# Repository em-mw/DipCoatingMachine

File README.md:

# DippingMachine

This is a instrument that is designed to dip an object into a solution

This instrument developed for TCH

-- em-mw

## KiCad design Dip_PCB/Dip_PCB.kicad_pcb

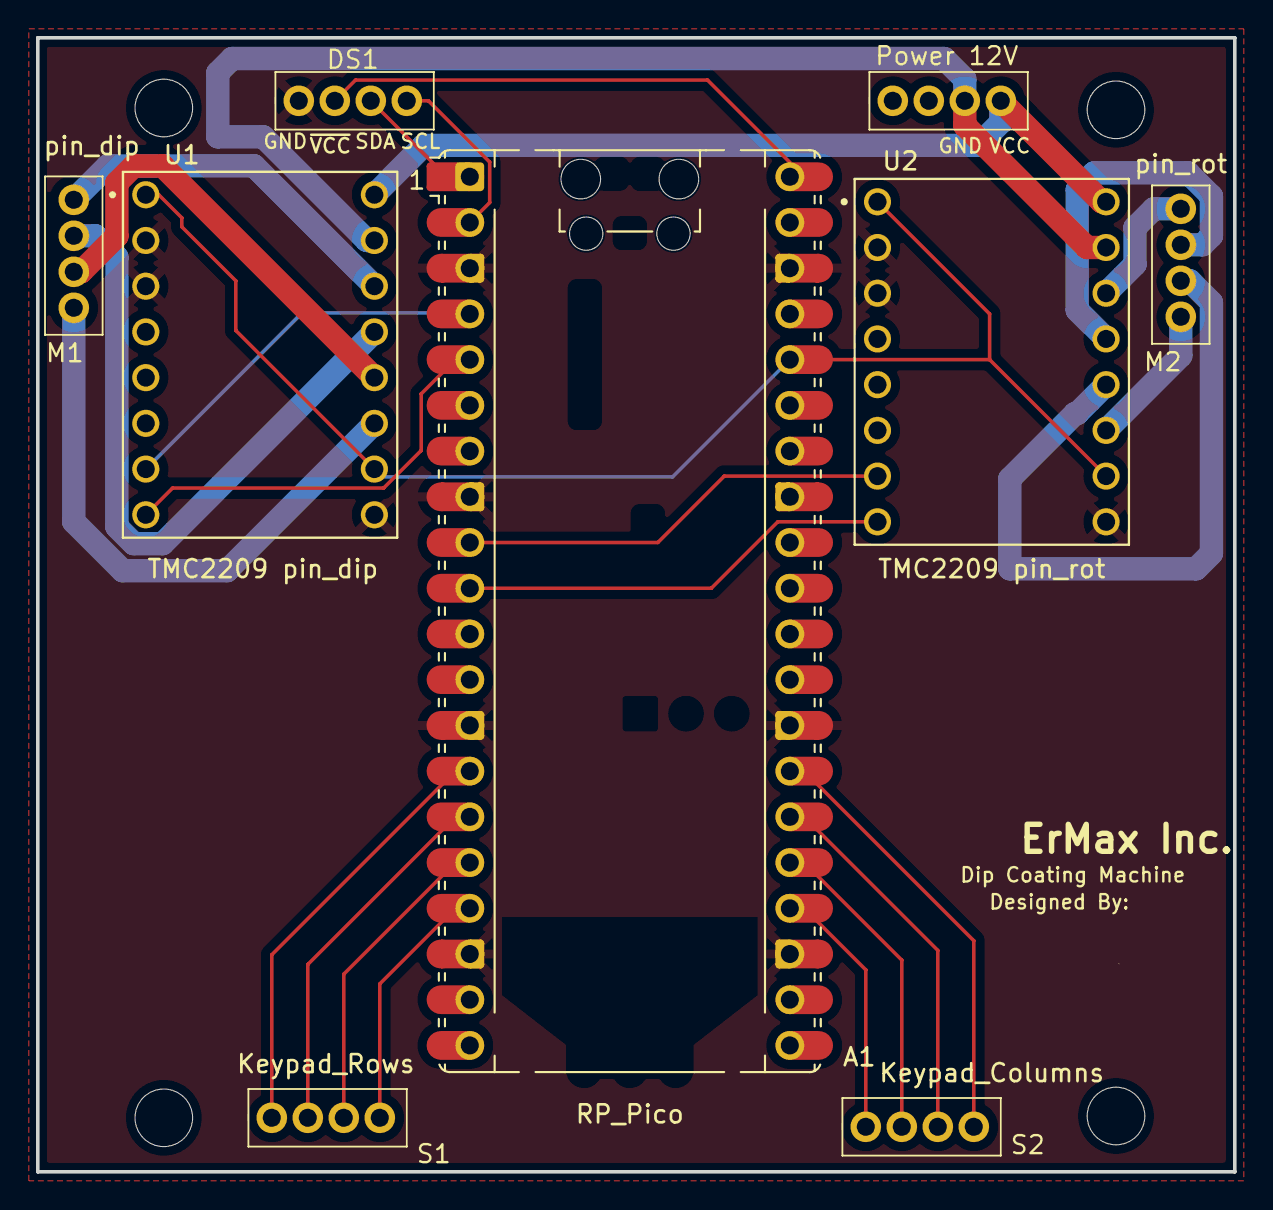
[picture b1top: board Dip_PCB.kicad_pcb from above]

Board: 2 copper layers, 66.5 x 63.0 mm, 9 parts (0 on the bottom side), 27 nets.

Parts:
A1: RP_Pico; RaspberryPi_Pico_Common_Unspecified
DS1: LCD; motor_footprint
M1: pin_dip; motor_footprint
M2: pin_rot; motor_footprint
Power 12V: motor_footprint
S1: Keypad_Rows; motor_footprint
S2: Keypad_Columns; motor_footprint
U1: TMC2209 pin_dip; MODULE_TMC2209_SILENTSTEPSTICK
U2: TMC2209 pin_rot; MODULE_TMC2209_SILENTSTEPSTICK

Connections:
unnamed: A1.1 (GPIO0), DS1.2 (SDA)
unnamed: A1.2 (GPIO1), DS1.1 (SCL)
unnamed: A1.4 (GPIO2), U1.7 (STEP)
unnamed: A1.5 (GPIO3), U1.8 (DIR)
unnamed: A1.9 (GPIO6), U2.7 (STEP)
unnamed: A1.10 (GPIO7), U2.8 (DIR)
unnamed: A1.14 (GPIO10), S1.4
unnamed: A1.15 (GPIO11), S1.3
unnamed: A1.16 (GPIO12), S1.2
unnamed: A1.17 (GPIO13), S1.1
unnamed: A1.24 (GPIO18), S2.4
unnamed: A1.25 (GPIO19), S2.3
unnamed: A1.26 (GPIO20), S2.2
unnamed: A1.27 (GPIO21), S2.1
unnamed: A1.40 (VBUS), DS1.3 (Vcc)
unnamed: M1.1, U1.14 (B2)
unnamed: M1.2, U1.13 (B1)
unnamed: M1.3, U1.12 (A1)
unnamed: M1.4, U1.11 (A2)
unnamed: M2.1, U2.14 (B2)
unnamed: M2.2, U2.13 (B1)
unnamed: M2.3, U2.12 (A1)
unnamed: M2.4, U2.11 (A2)
unnamed: Power 12V.2 (GND_12V), U1.10 (GND), U2.10 (GND)
VCC: Power 12V.1 (12V), U1.9 (VM), U2.9 (VM)
~GND: A1.3 (GND), A1.8 (GND), A1.13 (GND), A1.18 (GND), A1.23 (GND), A1.28 (GND), A1.38 (GND), DS1.4 (GND), U1.2 (MS1), U1.3 (MS2), U1.16 (GND), U2.2 (MS1), U2.3 (MS2), U2.16 (GND)
~VCC: A1.36 (3V3), U1.1 (~EN), U1.15 (~VDD), U2.1 (~EN), U2.15 (~VDD)
